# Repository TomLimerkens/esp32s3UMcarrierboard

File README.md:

# esp32s3UMcarrierboard
ESP32-S3 Carrier board for M.2 module from Unexpected Maker designed in KiCad

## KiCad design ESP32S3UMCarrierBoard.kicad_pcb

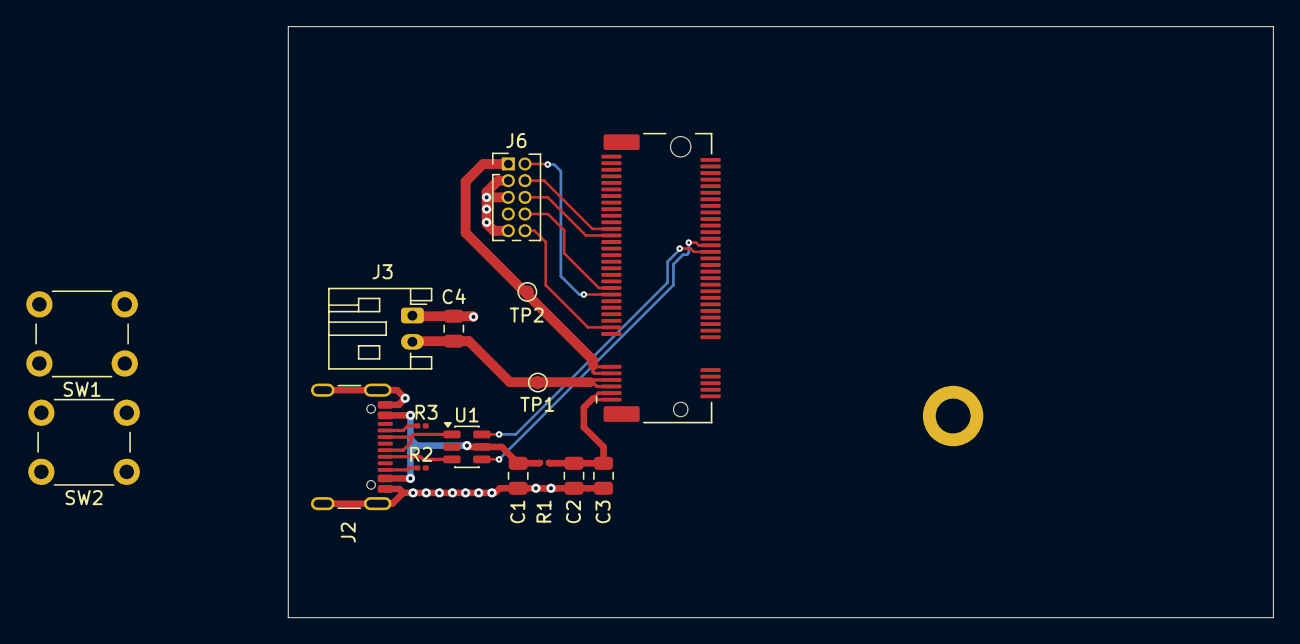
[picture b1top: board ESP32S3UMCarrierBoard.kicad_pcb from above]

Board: 2 copper layers, 75.0 x 45.0 mm, 16 parts (0 on the bottom side), 17 nets.

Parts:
C1, C2: 470n; C_0805_2012Metric
C3, C4: 10u; C_0805_2012Metric
J1: EDGES3D; EdgeS3D
J2: USB_C_Receptacle_USB2.0_16P; USB_C_Receptacle_GCT_USB4105-xx-A_16P_TopMnt_Horizontal
J3: Battery; JST_PH_S2B-PH-K_1x02_P2.00mm_Horizontal
J6: Conn_ARM_JTAG_SWD_10; PinHeader_2x05_P1.27mm_Vertical
R1: 0R; R_0201_0603Metric
R2, R3: 5k1; R_0201_0603Metric
SW1: BOOT; SW_PUSH_6mm
SW2: RESET; SW_PUSH_6mm
TP1, TP2: LiTo_TP_Small; TestPoint_Pad_D1.0mm
U1: USBLC6-2SC6; SOT-23-6

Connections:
+3V3: J1.9 (3V3), J1.11 (3V3), J6.1 (VTref), TP2.1
+BATT: C4.1, J1.5 (VBAT), J1.7 (VBAT), J3.2, TP1.1
+VBUS: C1.1, J2.A4 (VBUS), J2.A9 (VBUS), J2.B4 (VBUS), J2.B9 (VBUS), R1.1, U1.5 (VBUS)
+VUSB: C2.1, C3.1, J1.1 (5V), J1.3 (5V), R1.2
/CarrierBoard_BlockModel/JTAG_MTCK: J1.53 (IO39/MTCK), J6.4 (SWCLK/TCK)
/CarrierBoard_BlockModel/JTAG_MTDI: J1.35 (IO41/MTDI), J6.8 (NC/TDI)
/CarrierBoard_BlockModel/JTAG_MTDO: J1.51 (IO40/MTDO), J6.6 (SWO/TDO)
/CarrierBoard_BlockModel/JTAG_MTMS: J1.33 (IO42/MTMS), J6.2 (SWDIO/TMS)
/CarrierBoard_BlockModel/RESET: J1.23 (RESET), J6.10 (~RESET), SW2.2
/CarrierBoard_BlockModel/USBCD+: J2.A6 (D+), J2.B6 (D+), U1.3 (I/O2)
/CarrierBoard_BlockModel/USBCD-: J2.A7 (D-), J2.B7 (D-), U1.1 (I/O1)
/CarrierBoard_BlockModel/USB_D+: J1.48 (D+), U1.4 (I/O2)
/CarrierBoard_BlockModel/USB_D-: J1.46 (D-), U1.6 (I/O1)
GND: C1.2, C2.2, C3.2, C4.2, J1.2 (GND), J1.4 (GND), J1.6 (GND), J1.8 (GND), J1.10 (GND), J1.44 (GND), J1.50 (GND), J1.52 (GND), J1.54 (GND), J1.55 (GND), J1.56 (GND), J1.57 (GND), J1.59 (GND), J2.A1 (GND), J2.A12 (GND), J2.B1 (GND), J2.B12 (GND), J2.S1 (SHIELD), J3.1, J6.3 (GND), J6.5 (GND), J6.9 (GNDDetect), R2.2, R3.2, SW1.1, SW2.1, U1.2 (GND)
unnamed: J1.22 (IO0), SW1.2
unnamed: J2.A5 (CC1), R3.1
unnamed: J2.B5 (CC2), R2.1

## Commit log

2025-10-30 TemplateFolderStructure
2025-10-31 First pass schematic
    Components integrated
    Edge Library imported
    Basic functionality
    USB Integration done.
2025-10-31 test mfgr
2025-11-02 Added JTAG Debugging connection Added Battery Connection
2025-11-02 DFM Testrun at JLCPCB
2025-11-02 Adding TMC2209 Stepper Driver
2025-11-08 Boardconfig update
    updated board config
    updated outline
    moved USB and battery connections
